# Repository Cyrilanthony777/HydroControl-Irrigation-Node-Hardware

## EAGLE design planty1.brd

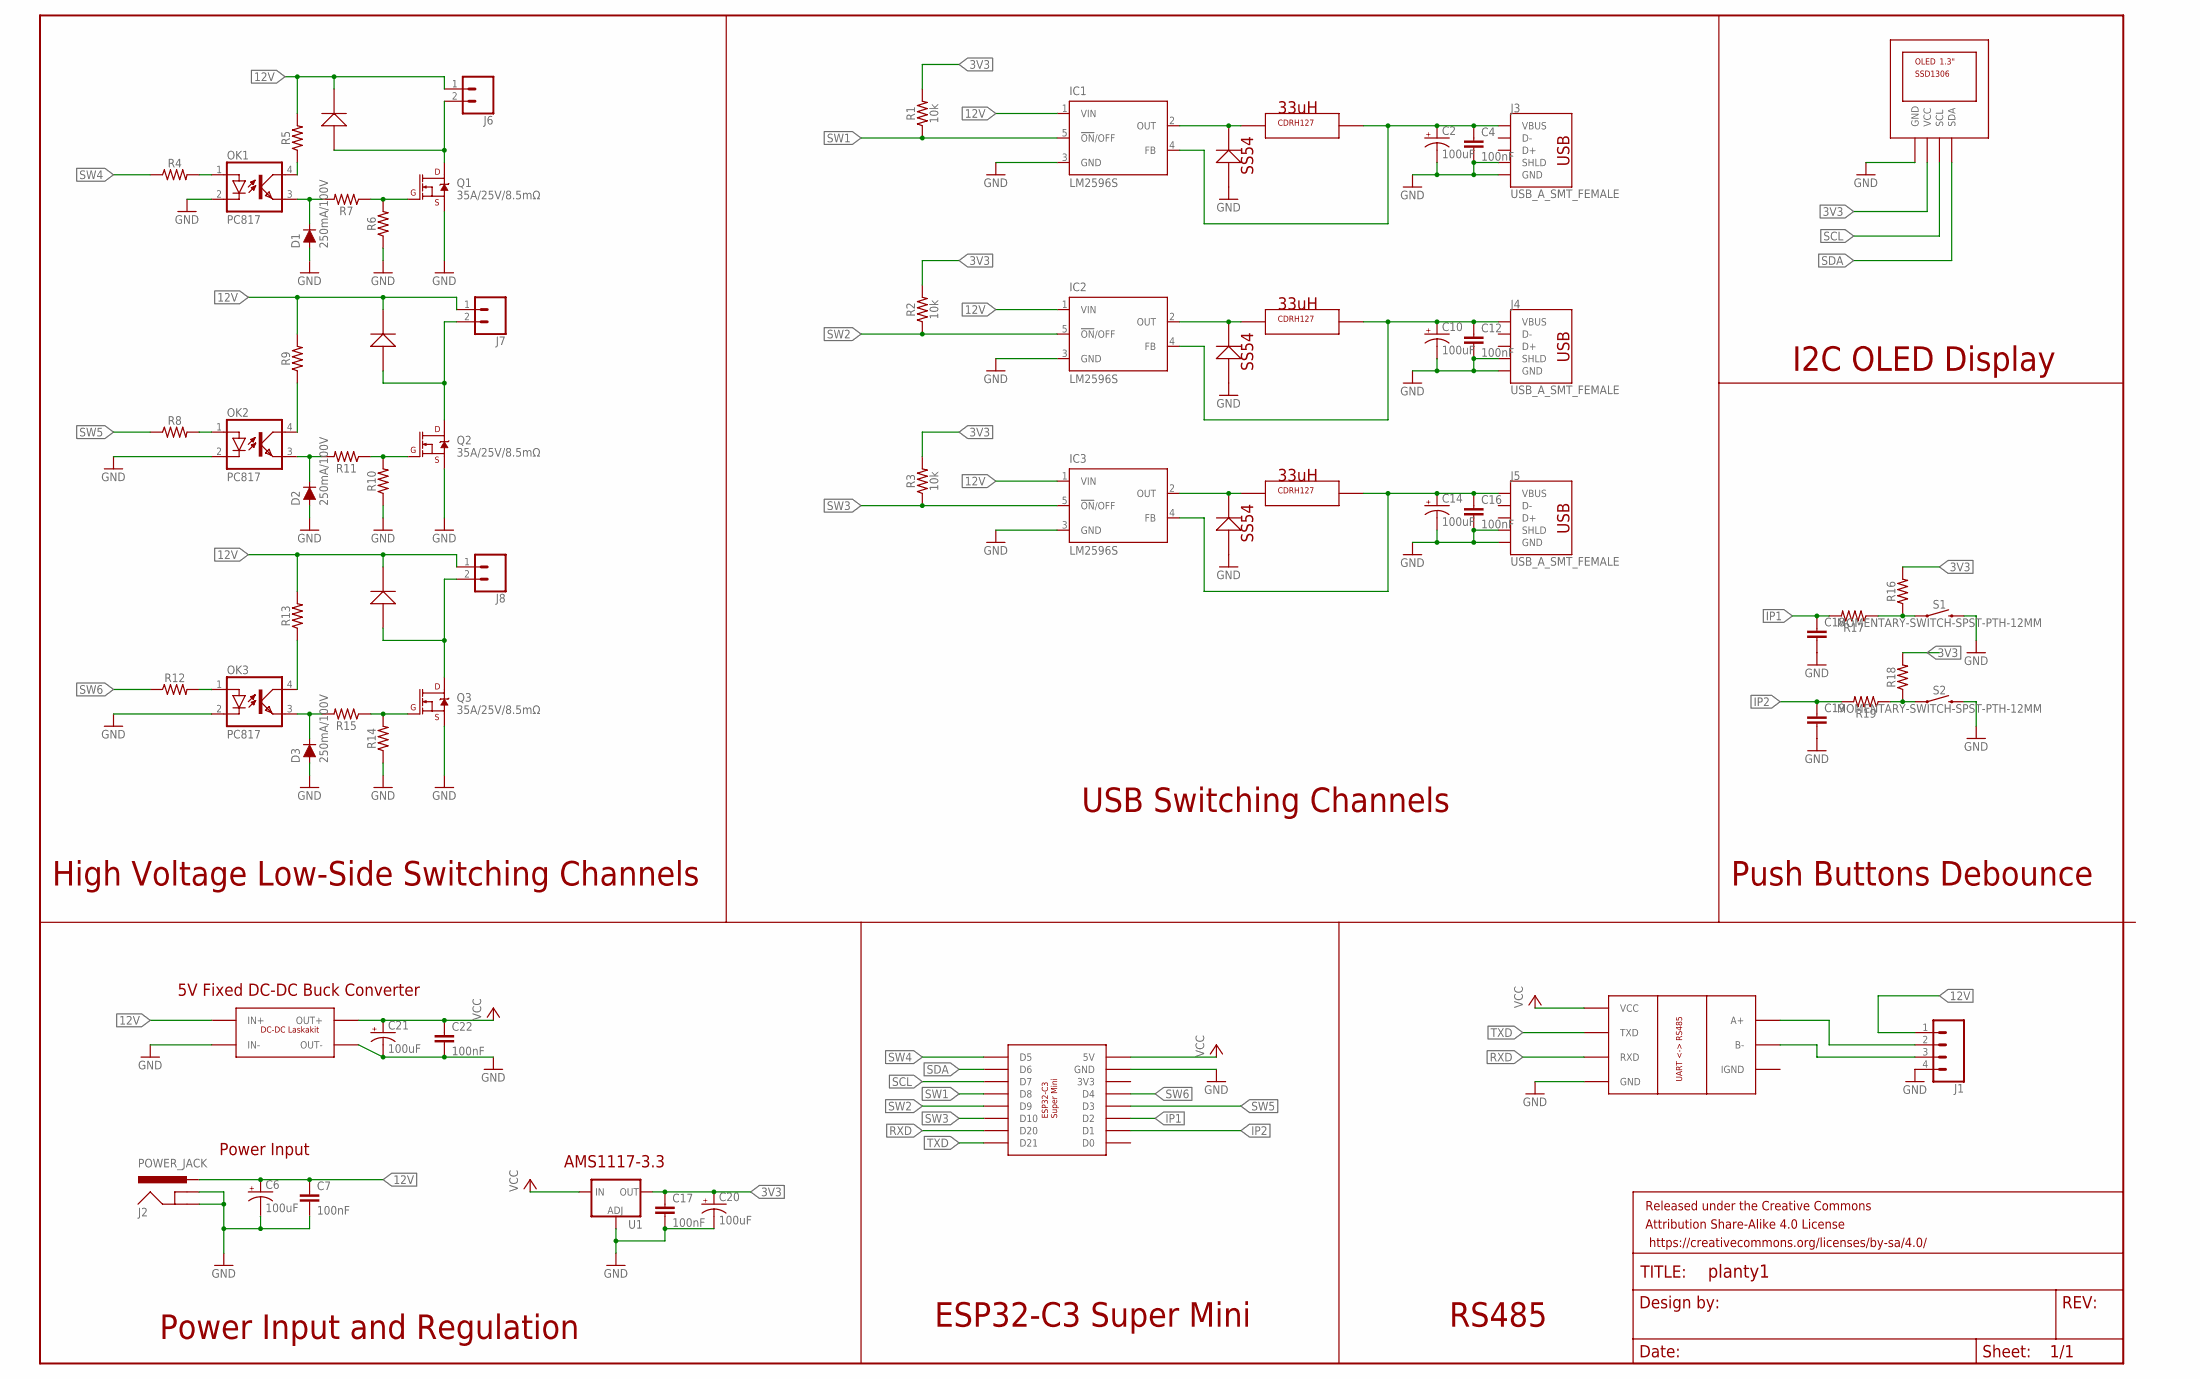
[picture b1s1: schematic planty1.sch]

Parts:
C2, C6, C10, C14, C20, C21: 100uF; CPOL-RADIAL-2.5MM-6.5MM
C4, C7, C12, C16, C22: 100nF; 1206
C17: 100nF; 0603
C18, C19: CAP-0603; 0603
D1, D2, D3: 250mA/100V; SOD-323
FRAME1: FRAME-LEDGERNO_FOOTPRINT; DUMMY
IC1, IC2, IC3: LM2596S; TO263-5
J1: CONN_04SCREW_LOCK; SCREWTERMINAL-3.5MM-4_LOCK
J2: POWER_JACK; POWER_JACK_PTH
J3, J4, J5: USB_A_SMT_FEMALE; USB-A-S-SILK-FEMALE
J6, J7, J8: CONN_025MM; SCREWTERMINAL-5MM-2
OK1, OK2, OK3: PC817; DIL04
Q1, Q2, Q3: 35A/25V/8.5mΩ; TO-252/DPAK
R1, R2, R3: 10k; 0603
R4, R5, R6, R7, R8, R9, R10, R11, R12, R13, R14, R15, R16, R17, R18, R19: 0603
S1, S2: MOMENTARY-SWITCH-SPST-PTH-12MM; TACTILE_SWITCH_PTH_12MM
U1: V_REG_LM1117SOT223; SOT223
U$1: ESP32-C3-SUPER-MINI
U$2: RS485-UART-CONVERTER; RS485_MODULE
U$3, U$6: CDRH127
U$4, U$7, U$9, U$10, U$11, U$12: SS54
U$5: DC-DC-LASKAKIT; DC-DC-MODULE-LASKAKIT
U$8: CDRH127 - 33uH; CDRH127
U$13: OLED_0.96_I2C; OLED_0.96

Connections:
3V3: C17.1, C20.1 (+), R1.2, R2.2, R3.2, R16.2, R18.2, U1.2 (OUT), U1.4 (OUT), U$13.P$2 (VCC)
12V: C6.1 (+), C7.1, IC1.1 (VIN), IC2.1 (VIN), IC3.1 (VIN), J1.1, J2.PWR, J6.1, J7.1, J8.1, R5.2, R9.2, R13.2, U$5.IN+, U$10.N, U$11.N, U$12.N
GND: C2.2 (-), C4.2, C6.2 (-), C7.2, C10.2 (-), C12.2, C14.2 (-), C16.2, C17.2, C18.2, C19.2, C20.2 (-), C21.2 (-), C22.2, D1.A, D2.A, D3.A, IC1.3 (GND), IC2.3 (GND), IC3.3 (GND), J1.4, J2.GND, J2.GNDBREAK, J3.GND, J3.SHLD1 (SHLD), J3.SHLD2 (SHLD), J4.GND, J4.SHLD1 (SHLD), J4.SHLD2 (SHLD), J5.GND, J5.SHLD1 (SHLD), J5.SHLD2 (SHLD), OK1.2 (C), OK2.2 (C), OK3.2 (C), Q1.3 (S), Q2.3 (S), Q3.3 (S), R6.1, R10.1, R14.1, S1.3 (2), S2.3 (2), U1.1 (ADJ), U$1.P$15 (GND), U$2.GND, U$4.P, U$5.IN-, U$5.OUT-, U$7.P, U$9.P, U$13.P$1 (GND)
IP1: C18.1, R17.2, U$1.P$11 (D2)
IP2: C19.1, R19.2, U$1.P$10 (D1)
unnamed: J1.2, U$2.A+
unnamed: J1.3, U$2.B-
unnamed: IC1.2 (OUT), U$3.P$1, U$4.N
unnamed: C2.1 (+), C4.1, IC1.4 (FB), J3.VBUS, U$3.P$2
unnamed: IC2.2 (OUT), U$6.P$1, U$7.N
unnamed: C10.1 (+), C12.1, IC2.4 (FB), J4.VBUS, U$6.P$2
unnamed: IC3.2 (OUT), U$8.P$1, U$9.N
unnamed: C14.1 (+), C16.1, IC3.4 (FB), J5.VBUS, U$8.P$2
unnamed: OK1.1 (A), R4.2
unnamed: OK1.4 (COL), R5.1
unnamed: Q1.1 (G), R6.2, R7.1
unnamed: D1.C, OK1.3 (EMIT), R7.2
unnamed: J6.2, Q1.2 (D), U$10.P
unnamed: OK2.1 (A), R8.2
unnamed: OK2.4 (COL), R9.1
unnamed: Q2.1 (G), R10.2, R11.1
unnamed: D2.C, OK2.3 (EMIT), R11.2
unnamed: J7.2, Q2.2 (D), U$11.P
unnamed: OK3.1 (A), R12.2
unnamed: OK3.4 (COL), R13.1
unnamed: Q3.1 (G), R14.2, R15.1
unnamed: D3.C, OK3.3 (EMIT), R15.2
unnamed: J8.2, Q3.2 (D), U$12.P
unnamed: R18.1, R19.1, S2.1
unnamed: R16.1, R17.1, S1.1
RXD: U$1.P$7 (D20), U$2.RXD
SCL: U$1.P$3 (D7), U$13.P$3 (SCL)
SDA: U$1.P$2 (D6), U$13.P$4 (SDA)
SW1: IC1.5 (!ON!/OFF), R1.1, U$1.P$4 (D8)
SW2: IC2.5 (!ON!/OFF), R2.1, U$1.P$5 (D9)
SW3: IC3.5 (!ON!/OFF), R3.1, U$1.P$6 (D10)
SW4: R4.1, U$1.P$1 (D5)
SW5: R8.1, U$1.P$12 (D3)
SW6: R12.1, U$1.P$13 (D4)
TXD: U$1.P$8 (D21), U$2.TXD
VCC: C21.1 (+), C22.1, U1.3 (IN), U$1.P$16 (5V), U$2.VCC, U$5.OUT+

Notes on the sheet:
High Voltage Low-Side Switching Channels
USB Switching Channels
33uH
SS54
AMS1117-3.3
5V Fixed DC-DC Buck Converter
Power Input
Power Input and Regulation
I2C OLED Display
Push Buttons Debounce
ESP32-C3 Super Mini
RS485

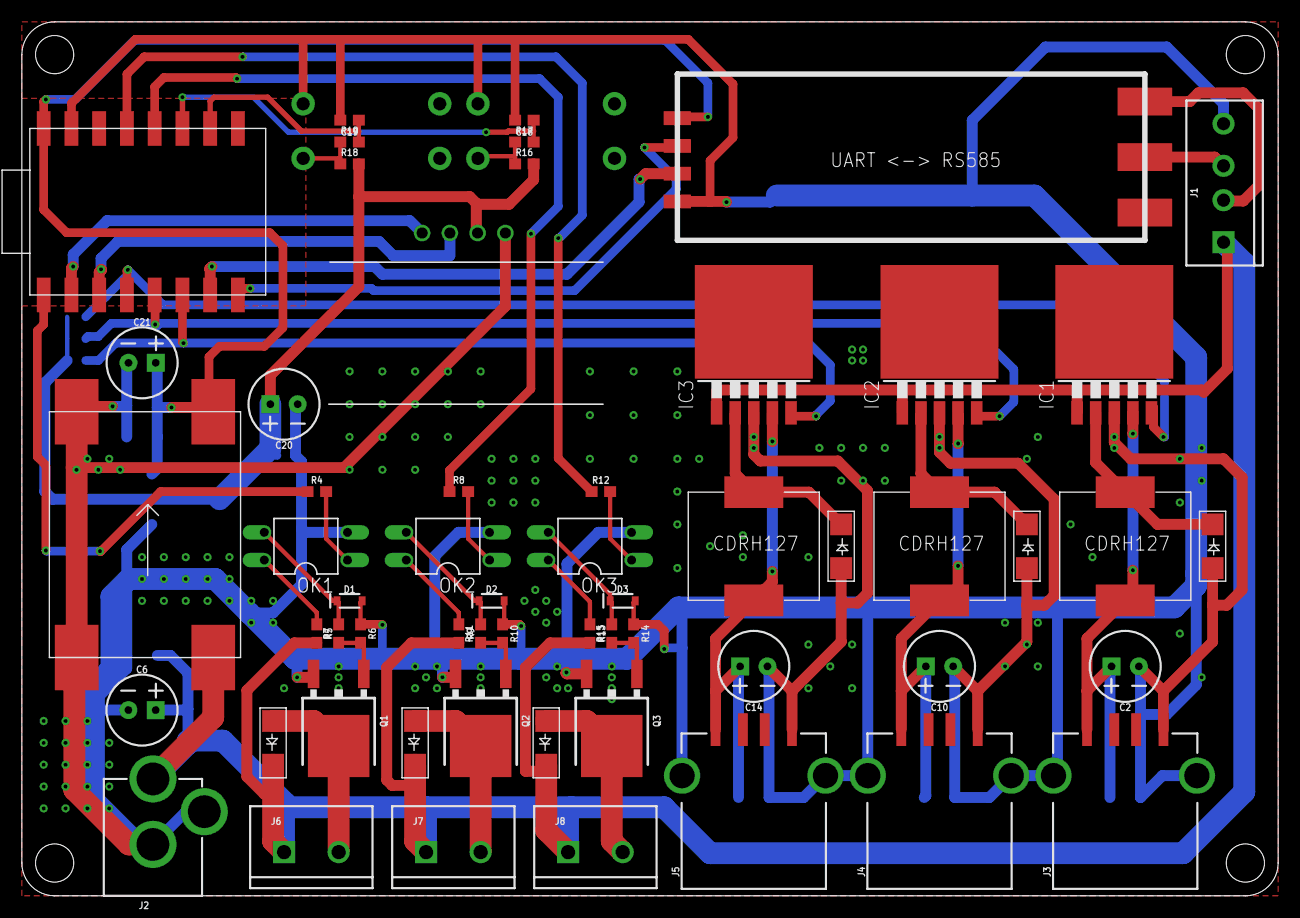
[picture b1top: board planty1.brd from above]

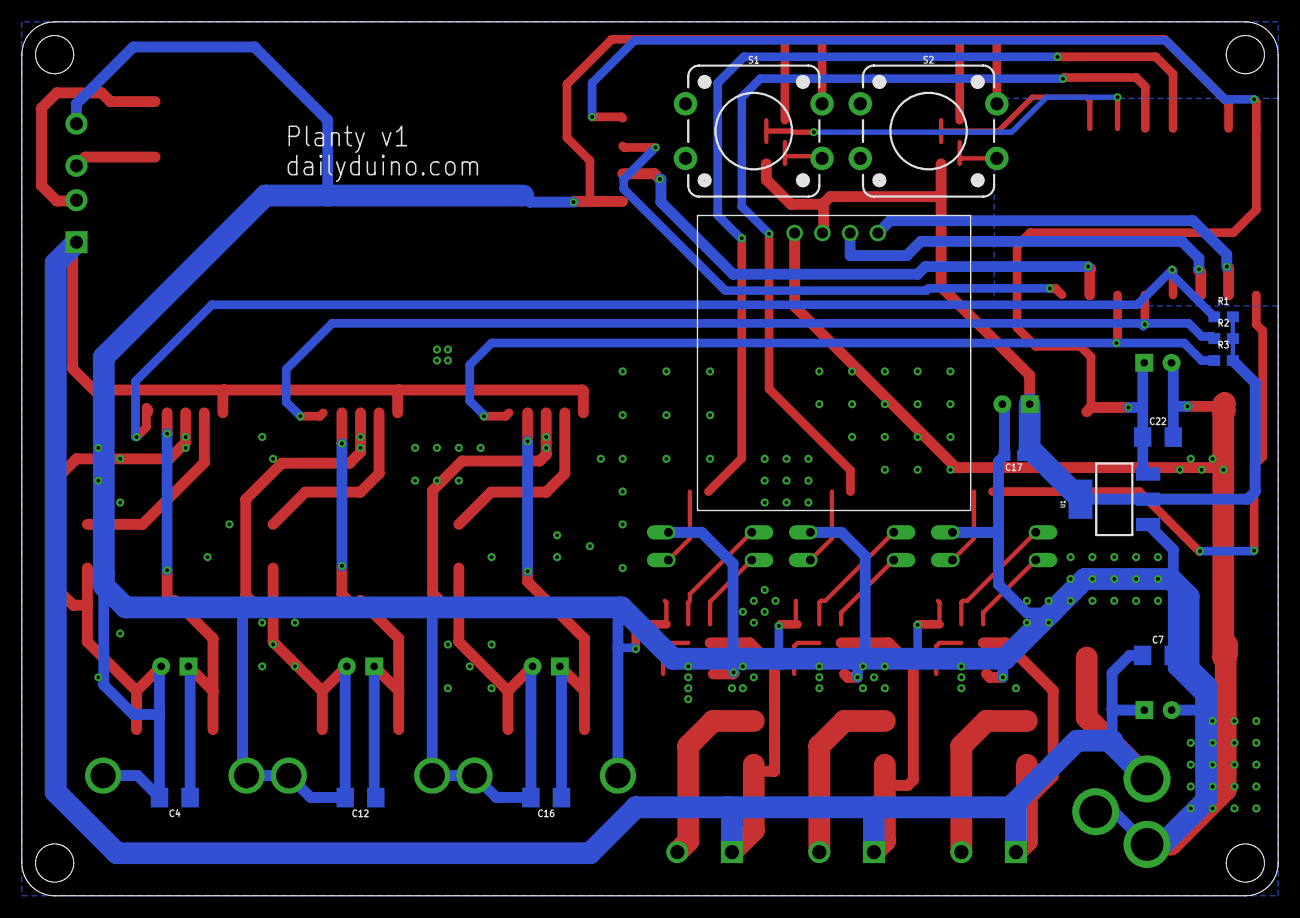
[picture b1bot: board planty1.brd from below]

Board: 2 copper layers, 115.0 x 80.0 mm, 70 parts (13 on the bottom side), 41 nets.

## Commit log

2025-07-16 initial
2025-07-17 schematic cleanup

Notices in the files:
parts and their libraries:
SparkFun-Capacitors: Licensing: Creative Commons ShareAlike 4.0 International - https://creativecommons.org/licenses/by-sa/4.0
SparkFun-Aesthetics: Released under the Creative Commons Attribution Share-Alike 4.0 License
SparkFun-Aesthetics: https://creativecommons.org/licenses/by-sa/4.0
